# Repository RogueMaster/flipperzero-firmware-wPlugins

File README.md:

# PC Health Remote

**Your PC's temperatures and load on a Flipper Zero, with vibration, sound and LED alerts when something goes wrong.**

PC Health Remote has two parts:

* a **Flipper Zero app** (`pc_health_remote`, category *Bluetooth*, v1.0) that shows the dashboard and raises alerts;
* a small **PC backend** (`pc-health-remote.exe`, written in Rust, a Windows tray app; Linux is best-effort) that reads
  your sensors and streams them to the Flipper over Bluetooth LE or USB.

English | [Русский](README.ru.md)

## Features

* **Temps page** - CPU and GPU temperature plus CPU, GPU, RAM and VRAM load bars.
* **Details page** - RAM and VRAM totals, CPU clock, fan speed, disk usage (%), battery, uptime,
  and the top CPU and top RAM process.
* **Alerts** - nine rules, each with its own on/off switch, threshold and signal
  (Vibro, Sound, Vib+Snd, LED, Off). The alert screen shows the current value versus the limit and 2 short tips.
  `OK` snoozes the alert for 10 minutes, `Back` closes it.
* **Bluetooth LE (default) or USB** transport. Settings are saved on the Flipper's SD card.
* **Silent reconnects** - pair once; afterwards the PC reconnects by itself whenever you open the app.
* **Autostart** - the backend can install itself as a Task Scheduler task that runs at logon.
* Works with the **official firmware** (SDK API 87.1, fw 1.4.3) and **RogueMaster** (API 88.4).

## How it works

The backend samples the PC about once a second and sends a fixed-size, CRC-protected telemetry frame to the
Flipper. The Flipper answers with a HELLO frame (which also tells the backend the update interval). If no valid
telemetry arrives for a while, the app shows "PC lost". The wire format is documented in
[docs/PROTOCOL.md](docs/PROTOCOL.md).

Sensor sources on Windows:

| Value | Source |
|-------|--------|
| CPU temperature | [LibreHardwareMonitor](https://github.com/LibreHardwareMonitor/LibreHardwareMonitor) via WMI if it is running (most accurate, CPU package); otherwise the Windows ACPI thermal zone |
| GPU temperature, load, VRAM | NVIDIA NVML - **NVIDIA GPUs only**; other GPUs show `--` |
| Fan RPM | LibreHardwareMonitor only |
| CPU/RAM/disk load, battery, uptime, processes | Windows |

## Quick start

Full walkthrough with screenshots: **[docs/SETUP.md](docs/SETUP.md)**.

1. **Install the Flipper app.** Get `pc_health_remote.fap` from the
   [latest release](https://github.com/ataman-lab/pc-health-remote/releases) and copy it to
   `/ext/apps/Bluetooth/` (for example with qFlipper -> *Install from file*), or install it from the Flipper app catalog.
2. **Download the backend.** Grab the Windows exe from the same
   [releases page](https://github.com/ataman-lab/pc-health-remote/releases) and put it somewhere permanent, for example
   `C:\Tools\pc-health-remote\pc-health-remote.exe` (the release asset is named
   `pc-health-remote-windows-x86_64.exe`; rename it if you like).
3. **Pair once.** Open *PC Health Remote* on the Flipper, then in PowerShell run:
   ```powershell
   .\pc-health-remote.exe pair
   ```
   The Flipper shows **Verify code** - press **OK** on the Flipper. Windows shows nothing; the backend accepts the
   request itself.
4. **Run it.** `.\pc-health-remote.exe` starts the tray app. Whenever the app is open on the Flipper, the connection is
   made automatically and silently.
5. **Autostart (optional).** From an **elevated** PowerShell, run once:
   ```powershell
   .\pc-health-remote.exe install
   ```
   This creates a Task Scheduler task that starts the backend at logon with highest privileges.
   `pc-health-remote.exe uninstall` removes it.

For the best CPU temperature (and fan speed), also run LibreHardwareMonitor - see [docs/SETUP.md](docs/SETUP.md).

> **Note:** On some newer CPUs (for example Intel Core Ultra 200HX / Arrow Lake laptops) Windows exposes no ACPI thermal zone, so CPU temperature stays at `--` unless LibreHardwareMonitor is running as administrator. LibreHardwareMonitor **0.9.6** did not publish sensors to WMI (`root\LibreHardwareMonitor` was missing) in testing; **0.9.4** (`LibreHardwareMonitor-net472.zip`) worked. Run `pc-health-remote.exe status` / check the log if the temperature is missing.

## Alerts and defaults

Press `OK` on the dashboard to open settings. Defaults:

| Rule | Default limit | Must hold for | Signal | Enabled |
|------|---------------|---------------|--------|---------|
| CPU temperature | 90 C | - | Vib+Snd | yes |
| GPU temperature | 85 C | - | Vib+Snd | yes |
| CPU load | 95 % | 30 s | Vibro | yes |
| GPU load | 98 % | 30 s | Vibro | **off** |
| RAM load | 90 % | 10 s | Vibro | yes |
| VRAM load | 95 % | 10 s | Vibro | yes |
| Disk used | 95 % | - | Sound | yes |
| Battery low | 20 % (only while on battery) | - | Vib+Snd | yes |
| PC link lost | 10 s without data | - | Vib+Snd | yes |

Limit and signal are adjustable per rule. Each rule can be switched on or off.

## Telegram alerts (beta)

Get the same alerts on your phone in Telegram, no Flipper needed. Bot: **@PCHealthRemoteBot**.

1. Open the bot and send `/link`. You get a 6-character code (valid 10 minutes).
2. On the PC run `pc-health-remote.exe --link-telegram <CODE>`.
3. Restart the backend. Alerts arrive as messages like `🔥 GAMING-PC: CPU temp 92°C (limit 90°C)`.

| | Free | Pro |
|---|---|---|
| PCs | 1 | 5 |
| Alerts per day | 10 | unlimited |
| Price | 0 | 99 Telegram Stars / 30 days (`/pro`) |

Details and privacy: [docs/TELEGRAM.md](docs/TELEGRAM.md).

Contact: [support@pchealthremote.com](mailto:support@pchealthremote.com) (bugs and ideas also welcome as [issues](https://github.com/ataman-lab/pc-health-remote/issues)).

## Command-line reference

```
pc-health-remote [run]      tray app (default)
pc-health-remote pair       pair with the Flipper (app must be open on it)
pc-health-remote unpair     forget the pairing
pc-health-remote metrics    print one JSON snapshot and where each value came from
pc-health-remote status     config, pairing, USB ports, task state, running instances
pc-health-remote install    create the logon task (run once, elevated)
pc-health-remote uninstall  remove the logon task
```

Useful flags: `--simulate` (synthetic changing values, handy for testing alerts), `--console` (show the log in a
console), `--transport auto|ble|usb`. More details in [backend/README.md](backend/README.md).

Config and log live in `%APPDATA%\pc-health-remote\` (`config.toml`, `log.txt`).

## Build from source

**Flipper app** (needs [ufbt](https://pypi.org/project/ufbt/)):

```bash
pip install ufbt
cd flipper
ufbt                 # builds dist/pc_health_remote.fap
ufbt launch          # build, upload and run on a connected Flipper
make -C tests        # host-side unit tests (protocol + alert engine)
```

To build against a custom firmware's SDK (for example RogueMaster), keep that SDK in its own directory by setting
`UFBT_HOME` before running `ufbt update` (use the SDK index/channel that firmware publishes; see
`ufbt update --help`), then build as usual:

```powershell
$env:UFBT_HOME = "C:\ufbt-custom-fw"
ufbt update --index-url=<SDK index URL of your firmware>
ufbt
```

Keep the same `UFBT_HOME` set for later builds so ufbt keeps using that SDK. The reference builds target the official
SDK (API 87.1) and RogueMaster (API 88.4).

**PC backend** (Rust 1.90 or newer):

```bash
cd backend
cargo build --release     # target/release/pc-health-remote(.exe)
cargo test
```

On Linux install `libdbus-1-dev libudev-dev pkg-config` first. The tray icon is Windows-only.

## Troubleshooting

See the troubleshooting table in [docs/SETUP.md](docs/SETUP.md#troubleshooting).

## Protocol

[docs/PROTOCOL.md](docs/PROTOCOL.md) describes the frames exchanged between the PC and the Flipper.

## Contributing

Issues are welcome - bug reports, hardware reports (firmware, Windows version, GPU) and ideas. An automated bot
triages new issues daily. Pull requests are appreciated; please run `make -C flipper/tests` and `cargo test` first.

## License

[MIT](LICENSE) (c) 2026 vladatman

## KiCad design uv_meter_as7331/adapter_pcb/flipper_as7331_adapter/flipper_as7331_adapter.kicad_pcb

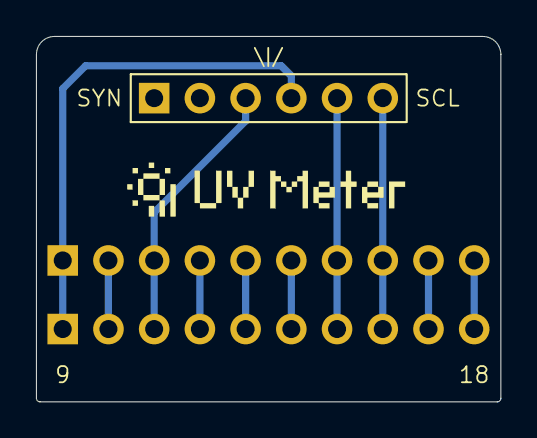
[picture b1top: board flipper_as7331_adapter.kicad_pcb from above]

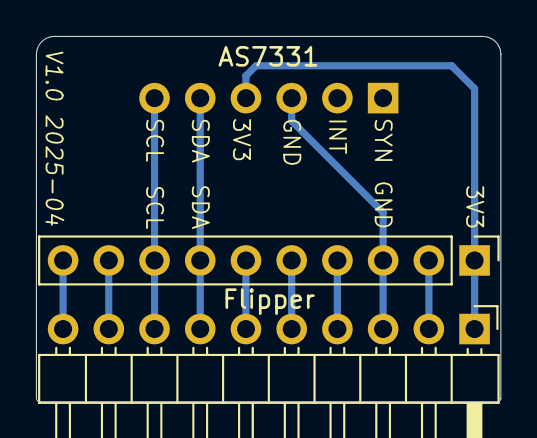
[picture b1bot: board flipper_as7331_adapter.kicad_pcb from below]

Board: 2 copper layers, 25.8 x 20.3 mm, 3 parts (2 on the bottom side), 10 nets.

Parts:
AS7331: AS7331; PinSocket_1x06_P2.54mm_Vertical
Flipper: Flipper; PinHeader_1x10_P2.54mm_Horizontal
J1: Conn_01x10; PinHeader_1x10_P2.54mm_Vertical

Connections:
unnamed: AS7331.3, Flipper.3, J1.3
unnamed: AS7331.4, Flipper.1, J1.1
unnamed: AS7331.5, Flipper.7, J1.7
unnamed: AS7331.6, Flipper.8, J1.8
unnamed: Flipper.2, J1.2
unnamed: Flipper.4, J1.4
unnamed: Flipper.5, J1.5
unnamed: Flipper.6, J1.6
unnamed: Flipper.9, J1.9
unnamed: Flipper.10, J1.10
